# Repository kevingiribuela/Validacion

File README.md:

# _Codigo para validar WIMUMO con la placa de la tesina_
Este es el código que se utilizó para validar que la placa realizada en la tesina responde correctamente a los requerimientos de WIMUMO, es decir, adquirir señales de biopotenciales y enviarlas por un socket a una computadora.
En el siguiente enlace se encuentra más información acerca de WIMUMO: https://gibic.ing.unlp.edu.ar/wimumo/

## Cómo utilizarlo
Para testearlo hay que setear el #define del software que se encuentra en el main.c a "#define PLACA 1" para aclarar que se va a utilizar la placa de la tesina. Luego se deben colocar los electrodos en sus conectores, y corroborar que la ganancia de los amplificadores operacionales que tiene la placa es acorde con la que cuenta el electrodo activo (que se colocará en el cuerpo). 
  Luego, una vez grabado el código, ESP32 se pondrá en modo AP para que se le ingrese a través de su WebServer los datos de la red a la que se debe conectar. Para ello se debe seguir los siguientes pasos:
  1) Conectarse a la red WiFi "Kevin Giribuela" con contraseña "senyt_unlp".
  2) Ingresar con un navegador a la dirección "192.168.4.1".
  3) Dentro de esa página se ingresan los datos de SSID, y PSWD de la red junto con el protocolo de transmisión (802.11b/bg/bgn).
  4) Apretar el botón de "Enviar datos!".
  5) Listo!
  
  Ahora, el ESP32 se conecta al red WiFi si todo salió bien, sino, se vuelve a poner en modo AP y se deben repetir los pasos anteriores.
  
  Una vez conectado, se debe abrir un Socket en el puerto 50 (está hardcodeado)
  Cuando el socket se haya abierto, se oprime el pulsador de propósito general de la placa y se habilita el envío de datos al socket. Si se desea detener la transmisión de datos se debe volver a presionar el pulsador de propósito general de la placa y el socket se cerrará. 

## Extras

Si ya se ha configurado una red en la placa, pero se la ha reiniciado, no es necesario volver a configurar la red a través del WebServer, simplemente hay que oprimir el pulsador de propósito general y la placa intentará conectarse automáticamente a la última red guardada.

# _PCB_
En la rama principal de este repositorio se encuentran los archivos de KiCAD V6 utilizados para la implementación del PCB.

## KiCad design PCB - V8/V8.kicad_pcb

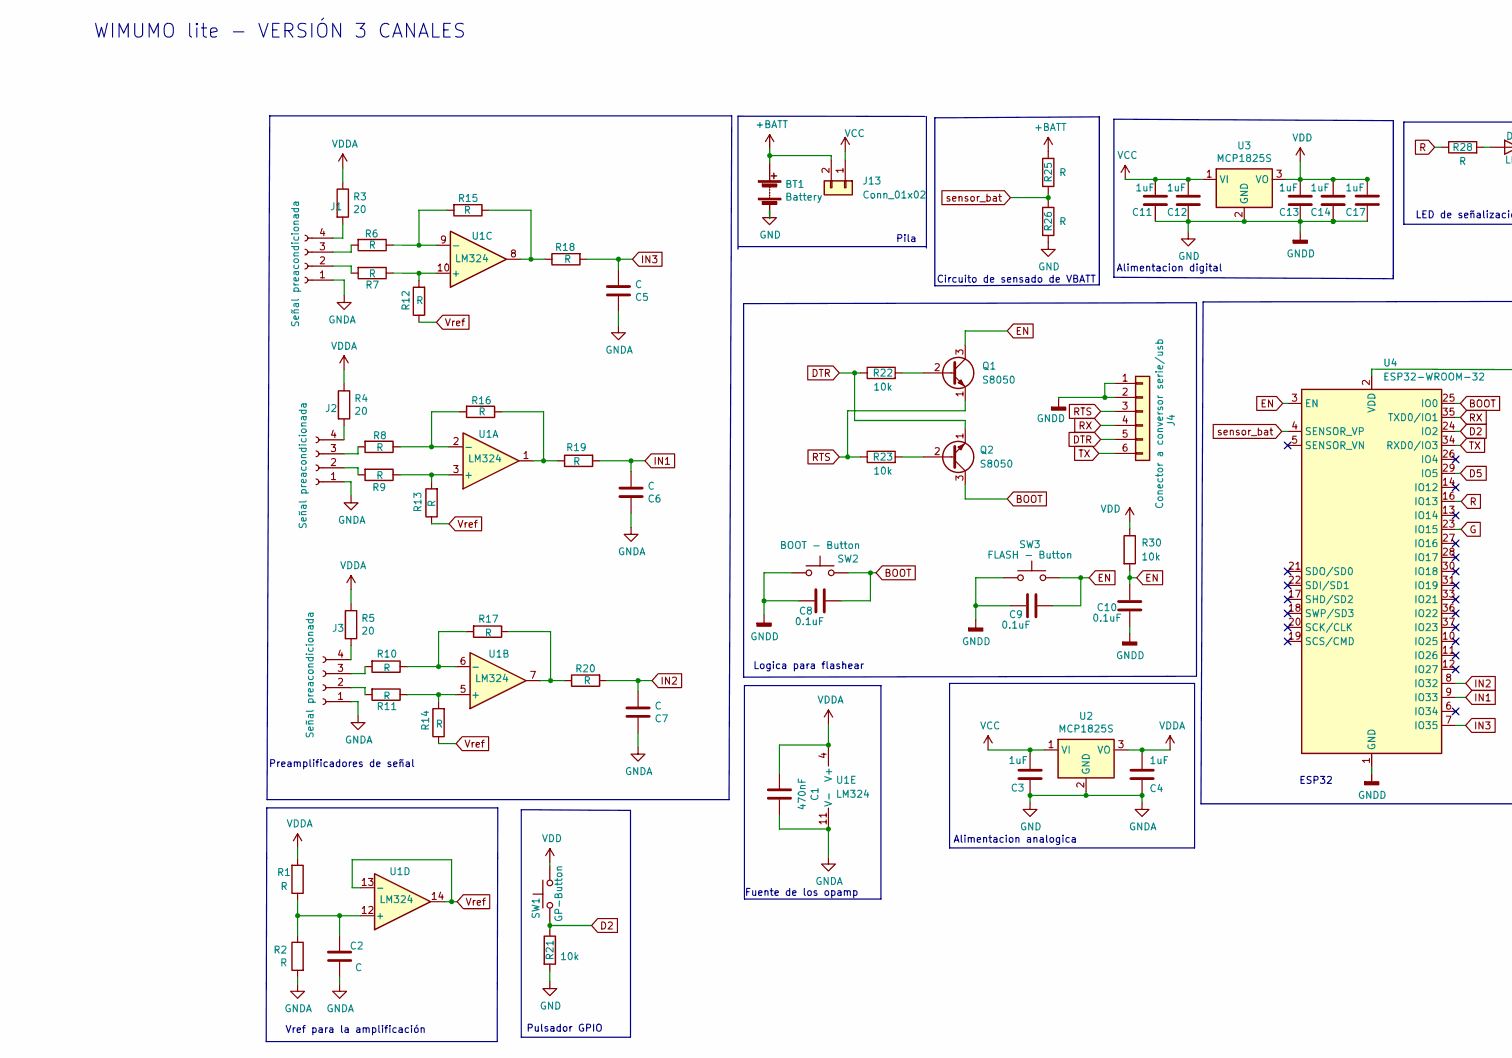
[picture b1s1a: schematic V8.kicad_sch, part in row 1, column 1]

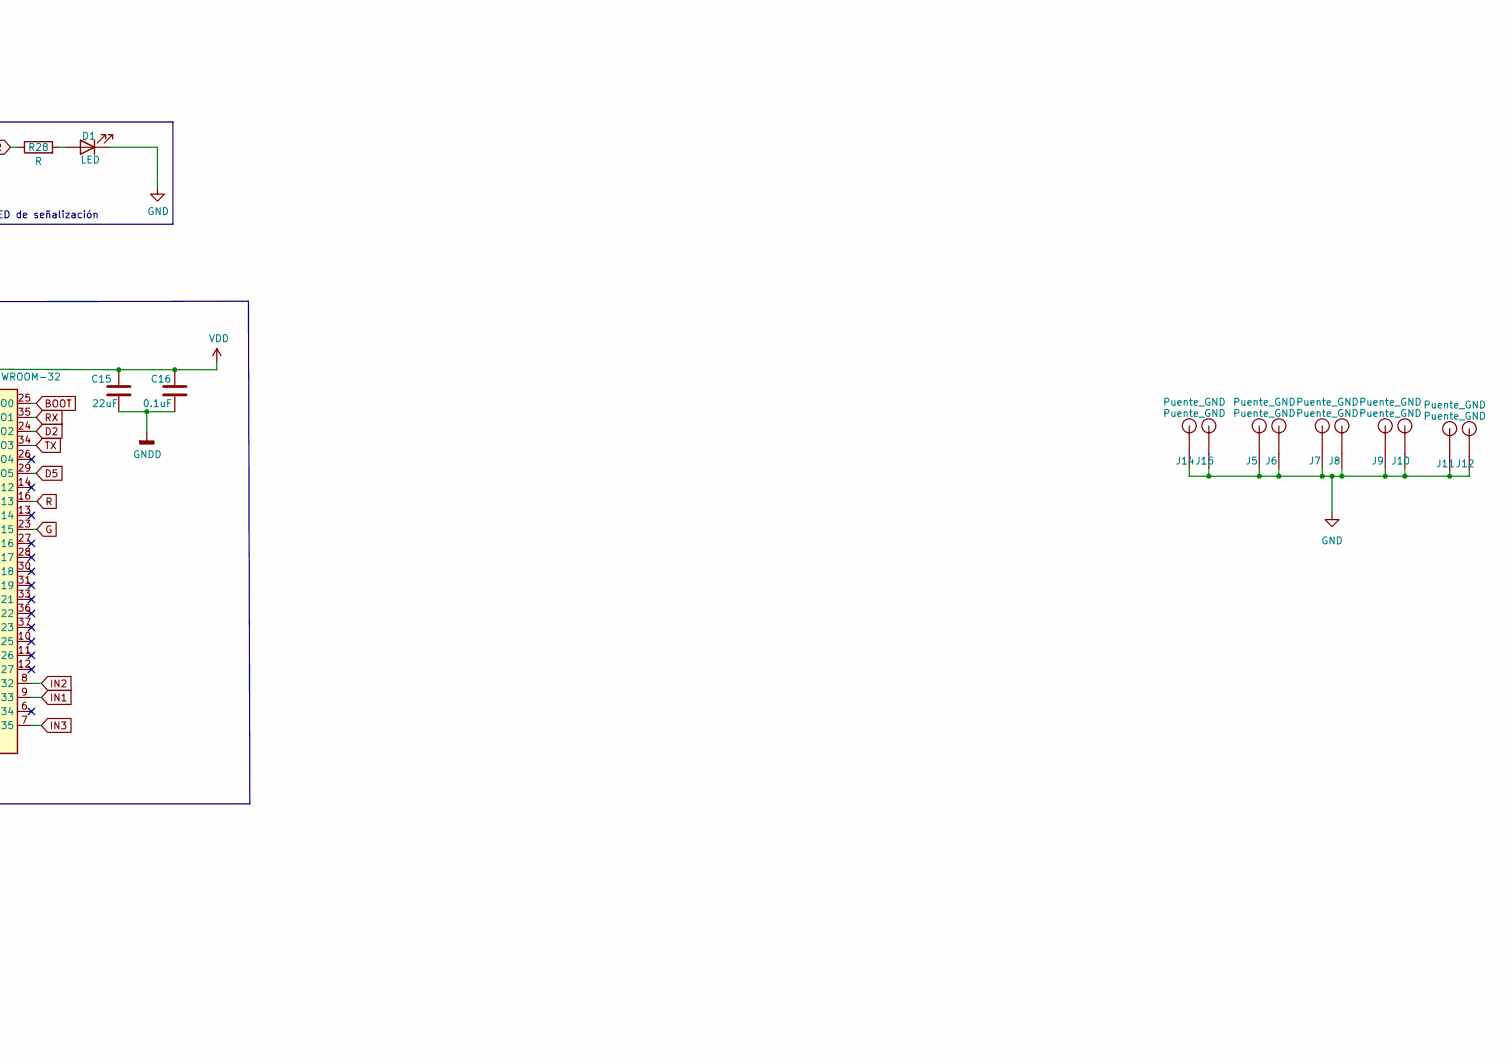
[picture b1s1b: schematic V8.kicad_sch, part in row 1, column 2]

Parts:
BT1: Battery; BatteryHolder_Keystone_2460_1xAA
C1: 470nF; C_0805_2012Metric
C2, C5, C6, C7: C; C_0805_2012Metric
C3, C4, C11, C12, C13, C14, C17: 1uF; C_0805_2012Metric
C8, C9, C10, C16: 0.1uF; C_0805_2012Metric
C15: 22uF; CP_EIA-3216-10_Kemet-I
D1: LED; LED_D3.0mm
J1, J2, J3: Señal preacondicionada; PinHeader_1x04_P2.54mm_Vertical
J4: Conector a conversor serie/usb; PinHeader_2x03_P2.54mm_Vertical
J5, J6, J7, J8, J9, J10, J11, J12, J14, J15: Puente_GND; PUENTE_GND
J13: Conn_01x02; PinHeader_1x02_P2.54mm_Vertical
Q1, Q2: S8050; SOT-23
R1, R2, R6, R7, R8, R9, R10, R11, R12, R13, R14, R15, R16, R17, R18, R19, R20, R25, R26, R28: R; R_0805_2012Metric
R3, R4, R5: 20; R_0805_2012Metric
R21, R22, R23, R30: 10k; R_0805_2012Metric
SW1: GP-Button; SW_PUSH_6mm
SW2: BOOT - Button; SW_PUSH_6mm
SW3: FLASH - Button; SW_PUSH_6mm
U1: LM324; SOIC-14_3.9x8.7mm_P1.27mm
U2, U3: MCP1825S; SOT-223-3_TabPin2
U4: ESP32-WROOM-32

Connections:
+BATT: BT1.1 (+), J13.2, R25.1
BOOT: C8.2, Q2.3 (C), SW2.2, U4.25 (IO0)
D2: R21.1, SW1.2, U4.24 (IO2)
D5: U4.29 (IO5)
DTR: J4.5, Q2.1 (E), R22.1
EN: C9.2, C10.2, Q1.3 (C), R30.2, SW3.2, U4.3 (EN)
G: U4.23 (IO15)
GND: BT1.2 (-), C1.1, C2.2, C3.2, C4.2, C5.1, C6.1, C7.1, C8.1, C9.1, C10.1, C11.2, C12.2, C13.2, C14.2, C15.1, C16.1, C17.2, D1.1 (K), J1.1, J2.1, J3.1, J4.1, J4.2, J5., J5.1, J6., J6.1, J7., J7.1, J8., J8.1, J9., J9.1, J10., J10.1, J11., J12., J12.1, J14., J14.1, J15., J15.1, R2.2, R21.2, R26.2, SW2.1, SW3.1, U1.11 (V-), U2.2 (GND), U3.2 (GND), U4.1 (GND), U4.15 (GND), U4.38 (GND), U4.39 (GND)
IN1: C6.2, R19.2, U4.9 (IO33)
IN2: C7.2, R20.2, U4.8 (IO32)
IN3: C5.2, R18.2, U4.7 (IO35)
unnamed: C2.1, R1.1, R2.1, U1.12 (+)
unnamed: D1.2 (A), R28.2
unnamed: J1.2, R7.2
unnamed: J1.3, R6.2
unnamed: J1.4, R3.2
unnamed: J2.2, R9.2
unnamed: J2.3, R8.2
unnamed: J2.4, R4.2
unnamed: J3.2, R11.2
unnamed: J3.3, R10.2
unnamed: J3.4, R5.2
unnamed: Q1.2 (B), R22.2
unnamed: Q2.2 (B), R23.2
unnamed: R10.1, R17.2, U1.6 (-)
unnamed: R11.1, R14.2, U1.5 (+)
unnamed: R7.1, R12.2, U1.10 (+)
unnamed: R9.1, R13.2, U1.3 (+)
unnamed: R15.1, R18.1, U1.8
unnamed: R6.1, R15.2, U1.9 (-)
unnamed: R16.1, R19.1, U1.1
unnamed: R8.1, R16.2, U1.2 (-)
unnamed: R17.1, R20.1, U1.7
R: R28.1, U4.16 (IO13)
RTS: J4.3, Q1.1 (E), R23.1
RX: J4.4, U4.35 (TXD0/IO1)
TX: J4.6, U4.34 (RXD0/IO3)
VCC: C3.1, C11.1, C12.1, J13.1, U2.1 (VI), U3.1 (VI)
VDD: C13.1, C14.1, C15.2, C16.2, C17.1, R30.1, SW1.1, U3.3 (VO), U4.2 (VDD)
VDDA: C1.2, C4.1, R1.2, R3.1, R4.1, R5.1, U1.4 (V+), U2.3 (VO)
Vref: R12.1, R13.1, R14.1, U1.13 (-), U1.14
sensor_bat: R25.2, R26.1, U4.4 (SENSOR_VP)

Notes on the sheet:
WIMUMO lite - VERSIÓN 3 CANALES
Pila
Alimentacion analogica
Pulsador GPIO
Fuente de los opamp
Vref para la amplificación
Logica para flashear
Circuito de sensado de VBATT
LED de señalización
Preamplificadores de señal
Alimentacion digital
ESP32

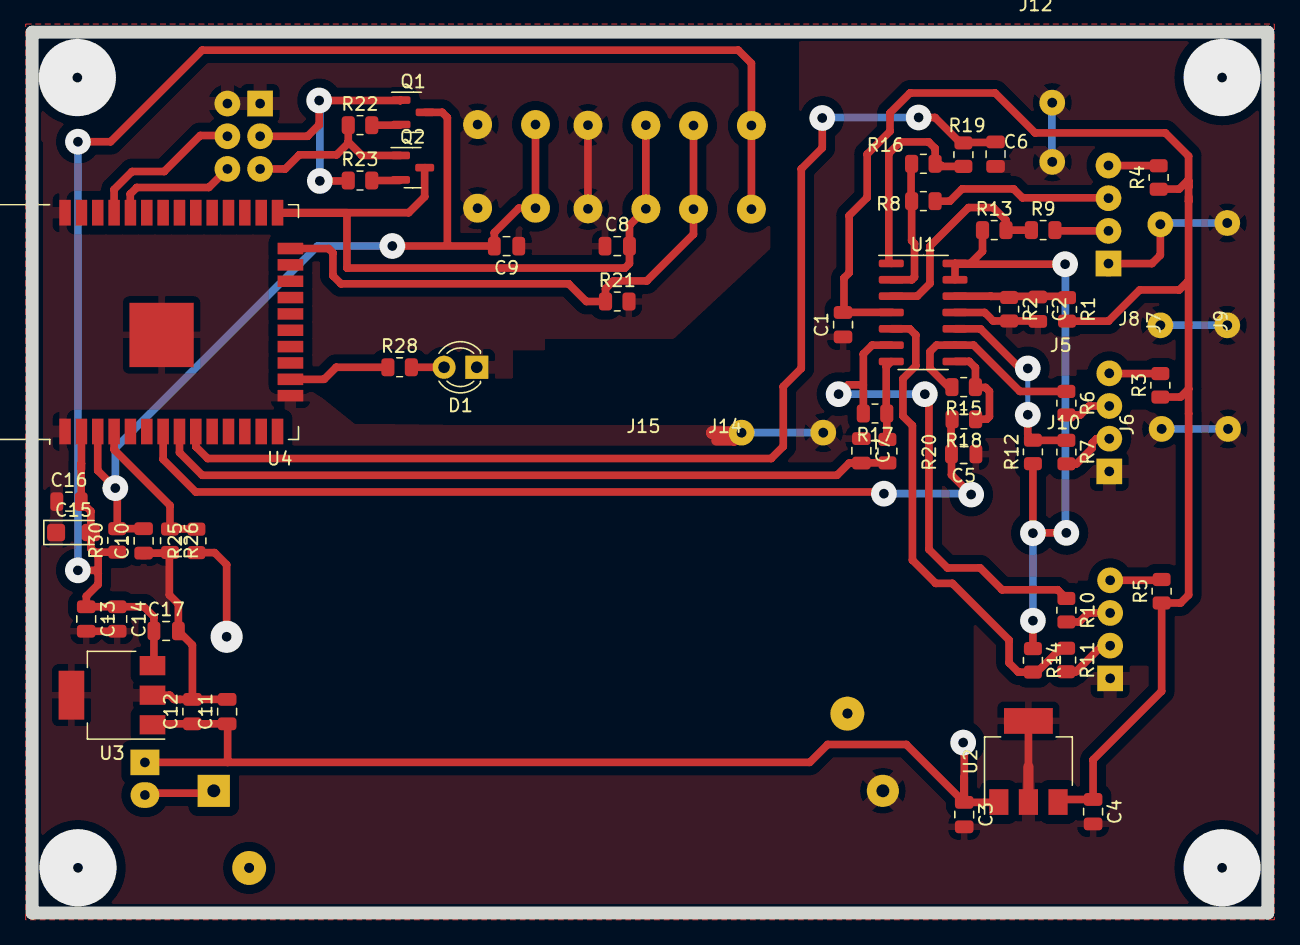
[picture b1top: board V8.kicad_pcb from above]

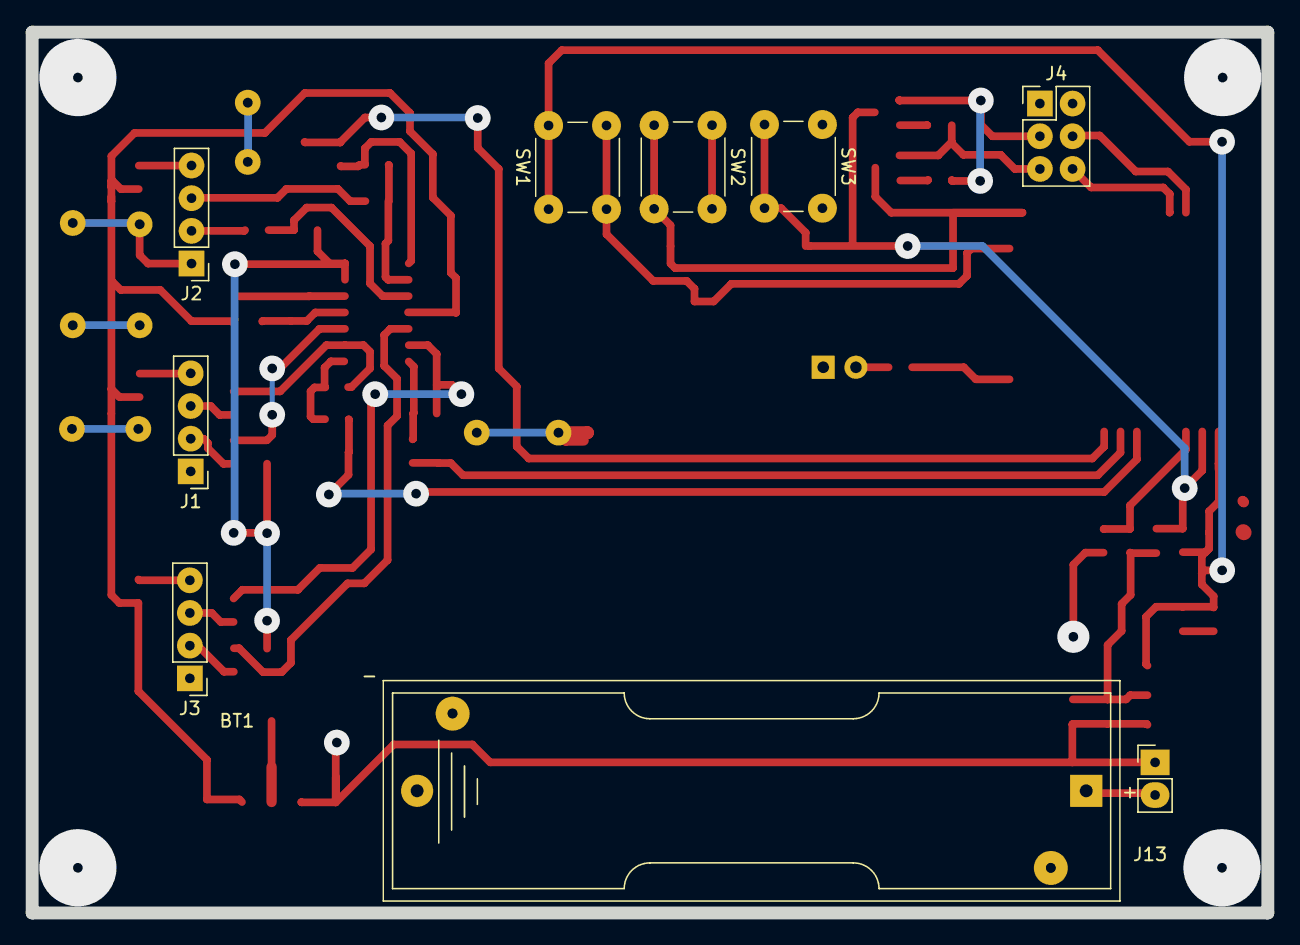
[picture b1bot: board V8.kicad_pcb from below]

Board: 2 copper layers, 96.0 x 68.4 mm, 70 parts (9 on the bottom side), 40 nets.

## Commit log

2022-10-28 Se añade el .html del webserver
    Contiene el código con dirección IP
2022-10-29 Se borra estado "enviar" para ganar velocidad
